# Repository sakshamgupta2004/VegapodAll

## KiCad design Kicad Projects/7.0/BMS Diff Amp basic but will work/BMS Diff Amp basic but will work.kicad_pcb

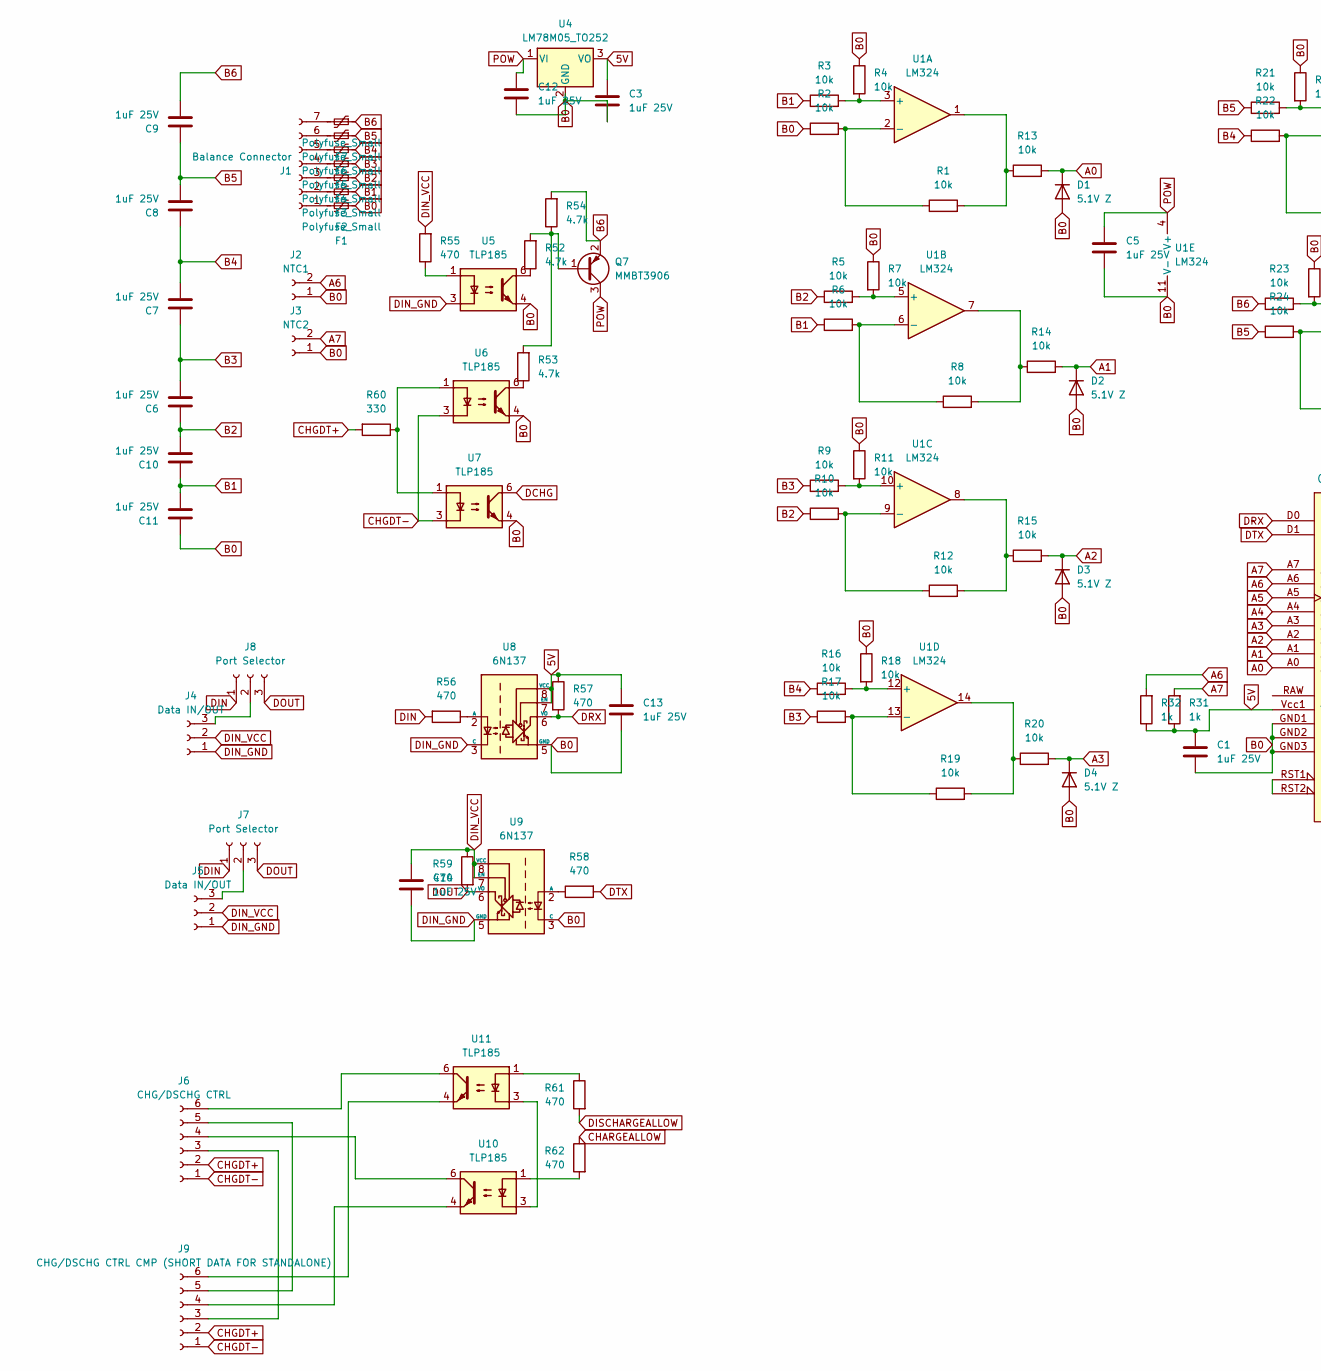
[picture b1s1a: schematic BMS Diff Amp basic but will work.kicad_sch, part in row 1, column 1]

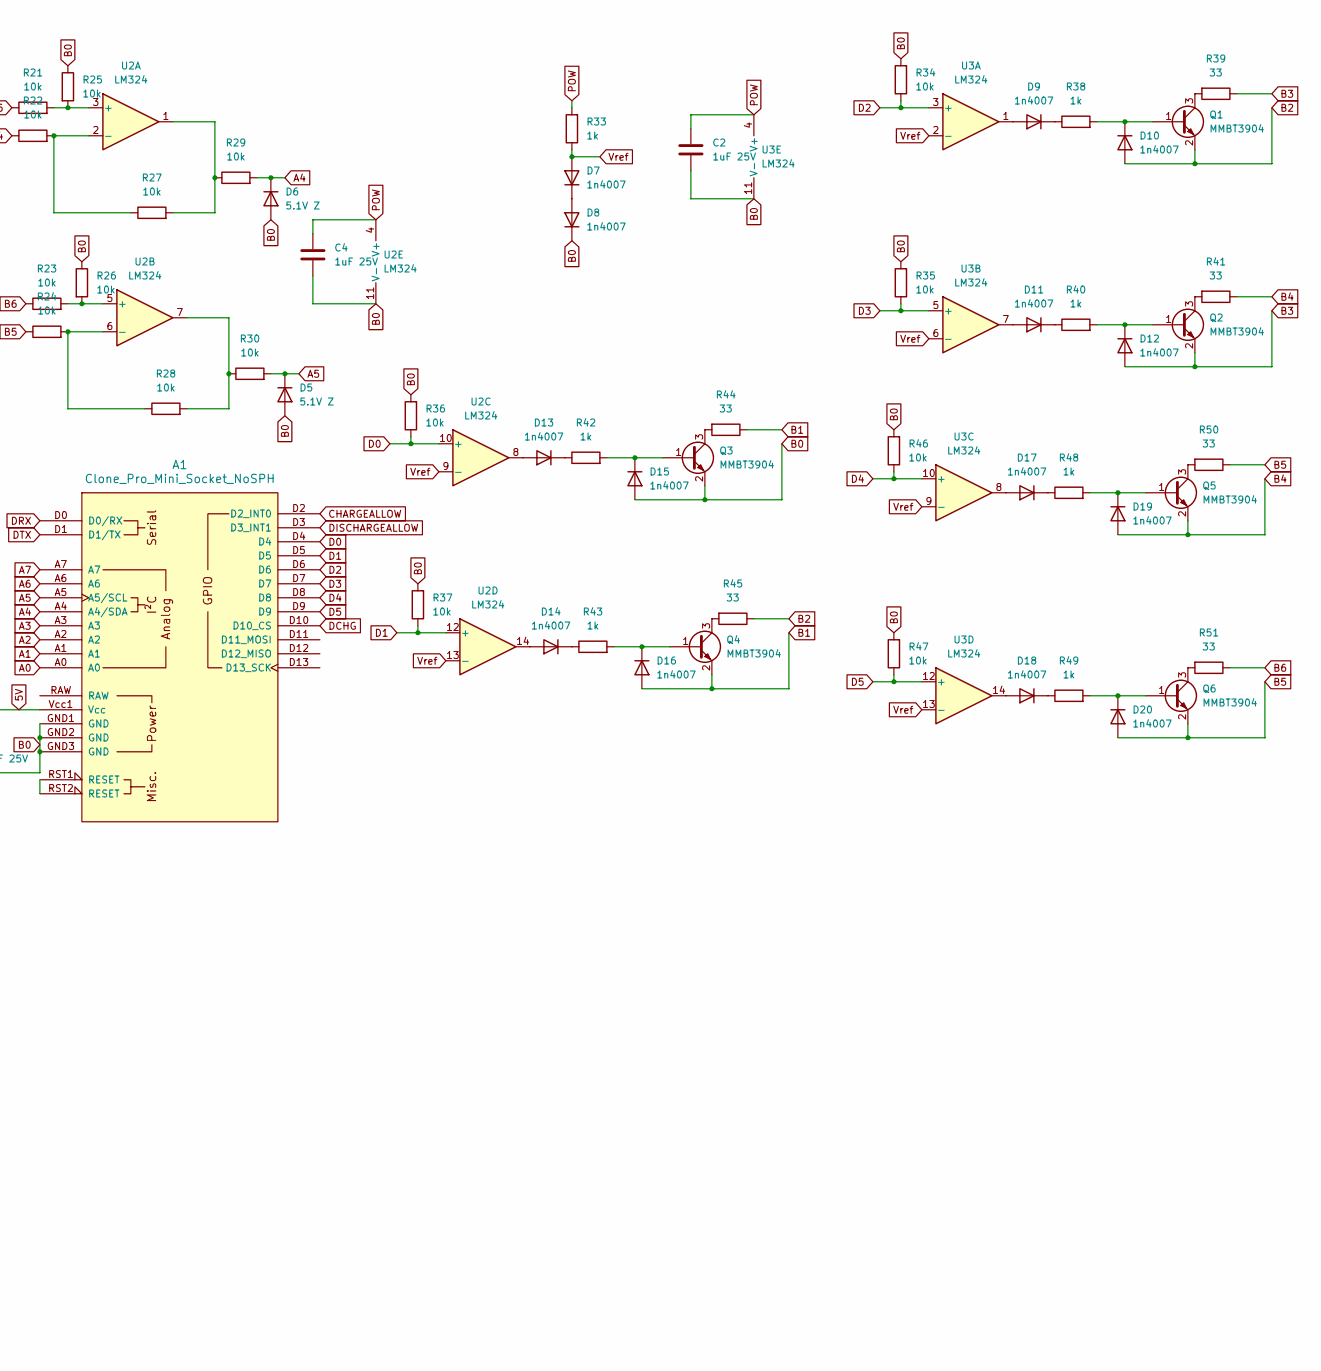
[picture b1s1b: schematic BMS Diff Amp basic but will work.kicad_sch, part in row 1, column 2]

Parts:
A1: Clone_Pro_Mini_Socket_NoSPH
C1, C2, C3, C4, C5, C6, C7, C8, C9, C10, C11, C12, C13, C14: 1uF 25V; C_1206_3216Metric_Pad1.33x1.80mm_HandSolder
D1, D2, D3, D4, D5, D6: 5.1V Z; D_SMA
D7, D8, D9, D10, D11, D12, D13, D14, D15, D16, D17, D18, D19, D20: 1n4007; D_SMA
F1, F2, F3, F4, F5, F6, F7: Polyfuse_Small; R_1206_3216Metric_Pad1.30x1.75mm_HandSolder
J1: Balance Connector; JST_XH_S7B-XH-A_1x07_P2.50mm_Horizontal
J2: NTC1; JST_XH_S2B-XH-A_1x02_P2.50mm_Horizontal
J3: NTC2; JST_XH_S2B-XH-A_1x02_P2.50mm_Horizontal
J4, J5: Data IN/OUT; JST_XH_S3B-XH-A-1_1x03_P2.50mm_Horizontal
J6: CHG/DSCHG CTRL; JST_XH_S6B-XH-A_1x06_P2.50mm_Horizontal
J7, J8: Port Selector; PinHeader_1x03_P1.00mm_Vertical
J9: CHG/DSCHG CTRL CMP (SHORT DATA FOR STANDALONE); JST_XH_B6B-XH-AM_1x06_P2.50mm_Vertical
Q1, Q2, Q3, Q4, Q5, Q6: MMBT3904; SOT-23
Q7: MMBT3906; SOT-23
R1, R2, R3, R4, R5, R6, R7, R8, R9, R10, R11, R12, R13, R14, R15, R16, R17, R18, R19, R20, R21, R22, R23, R24, R25, R26, R27, R28, R29, R30, R34, R35, R36, R37, R46, R47: 10k; R_0805_2012Metric_Pad1.20x1.40mm_HandSolder
R31, R32, R33, R38, R40, R42, R43, R48, R49: 1k; R_0805_2012Metric_Pad1.20x1.40mm_HandSolder
R39, R41, R44, R45, R50, R51: 33; R_1206_3216Metric_Pad1.30x1.75mm_HandSolder
R52, R53, R54: 4.7k; R_0805_2012Metric_Pad1.20x1.40mm_HandSolder
R55, R56, R57, R58, R59, R61, R62: 470; R_0805_2012Metric_Pad1.20x1.40mm_HandSolder
R60: 330; R_0805_2012Metric_Pad1.20x1.40mm_HandSolder
U1, U2, U3: LM324; SOIC-14_3.9x8.7mm_P1.27mm
U4: LM78M05_TO252; TO-252-2
U5, U6, U7, U10, U11: TLP185; SOIC-4_4.55x3.7mm_P2.54mm
U8, U9: 6N137; SOIC-8-1EP_3.9x4.9mm_P1.27mm_EP2.29x3mm

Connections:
5V: A1.Vcc1 (Vcc), C1.1, C3.1, C13.1, R31.1, R32.1, R57.1, U4.3 (VO), U8.7 (EN), U8.8 (VCC)
A0: A1.A0, D1.1 (K), R13.2
A1: A1.A1, D2.1 (K), R14.2
A2: A1.A2, D3.1 (K), R15.2
A3: A1.A3, D4.1 (K), R20.2
A4: A1.A4 (A4/SDA), D6.1 (K), R29.2
A5: A1.A5 (A5/SCL), D5.1 (K), R30.2
A6: A1.A6, J2.2, R32.2
A7: A1.A7, J3.2, R31.2
B0: A1.GND1 (GND), A1.GND2 (GND), A1.GND3 (GND), C1.2, C2.2, C3.2, C4.2, C5.2, C11.1, C12.2, C13.2, D1.2 (A), D2.2 (A), D3.2 (A), D4.2 (A), D5.2 (A), D6.2 (A), D8.1 (K), D15.2 (A), F1.1, J2.1, J3.1, Q3.2 (E), R2.1, R4.1, R7.1, R11.1, R18.1, R25.1, R26.1, R34.2, R35.2, R36.2, R37.2, R46.2, R47.2, U1.11 (V-), U2.11 (V-), U3.11 (V-), U4.2 (GND), U5.4, U6.4, U7.4, U8.5 (GND), U9.3 (C)
B1: C10.1, C11.2, D16.2 (A), F2.1, Q4.2 (E), R3.1, R6.1, R44.1
B2: C6.1, C10.2, D10.2 (A), F3.1, Q1.2 (E), R5.1, R10.1, R45.1
B3: C6.2, C7.1, D12.2 (A), F4.1, Q2.2 (E), R9.1, R17.1, R39.1
B4: C7.2, C8.1, D19.2 (A), F5.1, Q5.2 (E), R16.1, R22.1, R41.1
B5: C8.2, C9.1, D20.2 (A), F6.1, Q6.2 (E), R21.1, R24.1, R50.1
B6: C9.2, F7.1, Q7.2 (E), R23.1, R51.1, R54.2
CHARGEALLOW: A1.D2 (D2_INT0), R62.1
CHGDT+: J6.2, J9.2, R60.2
CHGDT-: J6.1, J9.1, U6.3, U7.3
D0: A1.D4, R36.1, U2.10 (+)
D1: A1.D5, R37.1, U2.12 (+)
D2: A1.D6, R34.1, U3.3 (+)
D3: A1.D7, R35.1, U3.5 (+)
D4: A1.D8, R46.1, U3.10 (+)
D5: A1.D9, R47.1, U3.12 (+)
DCHG: A1.D10 (D10_CS), U7.6
DIN: J7.1, J8.1, R56.2
DIN_GND: C14.2, J4.1, J5.1, U5.3, U8.3 (C), U9.5 (GND)
DIN_VCC: C14.1, J4.2, J5.2, R55.2, R59.1, U9.7 (EN), U9.8 (VCC)
DISCHARGEALLOW: A1.D3 (D3_INT1), R61.2
DOUT: J7.3, J8.3, R59.2, U9.6 (VO)
DRX: A1.D0 (D0/RX), R57.2, U8.6 (VO)
DTX: A1.D1 (D1/TX), R58.2
unnamed: A1.RST1 (RESET), A1.RST2 (RESET)
unnamed: D7.1 (K), D8.2 (A)
unnamed: D9.2 (A), U3.1
unnamed: D9.1 (K), R38.1
unnamed: D10.1 (K), Q1.1 (B), R38.2
unnamed: D11.2 (A), U3.7
unnamed: D11.1 (K), R40.1
unnamed: D12.1 (K), Q2.1 (B), R40.2
unnamed: D13.2 (A), U2.8
unnamed: D13.1 (K), R42.1
unnamed: D14.2 (A), U2.14
unnamed: D14.1 (K), R43.1
unnamed: D15.1 (K), Q3.1 (B), R42.2
unnamed: D16.1 (K), Q4.1 (B), R43.2
unnamed: D17.2 (A), U3.8
unnamed: D17.1 (K), R48.1
unnamed: D18.2 (A), U3.14
unnamed: D18.1 (K), R49.1
unnamed: D19.1 (K), Q5.1 (B), R48.2
unnamed: D20.1 (K), Q6.1 (B), R49.2
unnamed: F1.2, J1.1
unnamed: F2.2, J1.2
unnamed: F3.2, J1.3
unnamed: F4.2, J1.4
unnamed: F5.2, J1.5
unnamed: F6.2, J1.6
unnamed: F7.2, J1.7
unnamed: J4.3, J8.2
unnamed: J5.3, J7.2
unnamed: J6.3, J9.3
unnamed: J6.4, U10.6
unnamed: J6.5, J9.5
unnamed: J6.6, U11.6
unnamed: J9.4, U10.4
unnamed: J9.6, U11.4
unnamed: Q1.3 (C), R39.2
unnamed: Q2.3 (C), R41.2
unnamed: Q3.3 (C), R44.2
unnamed: Q4.3 (C), R45.2
unnamed: Q5.3 (C), R50.2
unnamed: Q6.3 (C), R51.2
unnamed: Q7.1 (B), R52.2, R53.2, R54.1
unnamed: R1.2, R13.1, U1.1
unnamed: R12.2, R15.1, U1.8
unnamed: R8.2, R14.1, U1.7
unnamed: R19.2, R20.1, U1.14
unnamed: R27.2, R29.1, U2.1
unnamed: R28.2, R30.1, U2.7
unnamed: R52.1, U5.6
unnamed: R53.1, U6.6
unnamed: R55.1, U5.1
unnamed: R60.1, U6.1, U7.1
unnamed: R61.1, U11.1
unnamed: R62.2, U10.1
unnamed: R3.2, R4.2, U1.3 (+)
unnamed: R1.1, R2.2, U1.2 (-)
unnamed: R5.2, R7.2, U1.5 (+)
unnamed: R6.2, R8.1, U1.6 (-)
unnamed: R9.2, R11.2, U1.10 (+)
unnamed: R10.2, R12.1, U1.9 (-)
unnamed: R16.2, R18.2, U1.12 (+)
unnamed: R17.2, R19.1, U1.13 (-)
unnamed: R21.2, R25.2, U2.3 (+)
unnamed: R22.2, R27.1, U2.2 (-)
unnamed: R23.2, R26.2, U2.5 (+)
unnamed: R24.2, R28.1, U2.6 (-)
unnamed: R56.1, U8.2 (A)
unnamed: R58.1, U9.2 (A)
unnamed: U10.3, U11.3
POW: C2.1, C4.1, C5.1, C12.1, Q7.3 (C), R33.2, U1.4 (V+), U2.4 (V+), U3.4 (V+), U4.1 (VI)
Vref: D7.2 (A), R33.1, U2.9 (-), U2.13 (-), U3.2 (-), U3.6 (-), U3.9 (-), U3.13 (-)

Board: 2 copper layers, 131 parts (0 on the bottom side), 104 nets, no tracks yet.

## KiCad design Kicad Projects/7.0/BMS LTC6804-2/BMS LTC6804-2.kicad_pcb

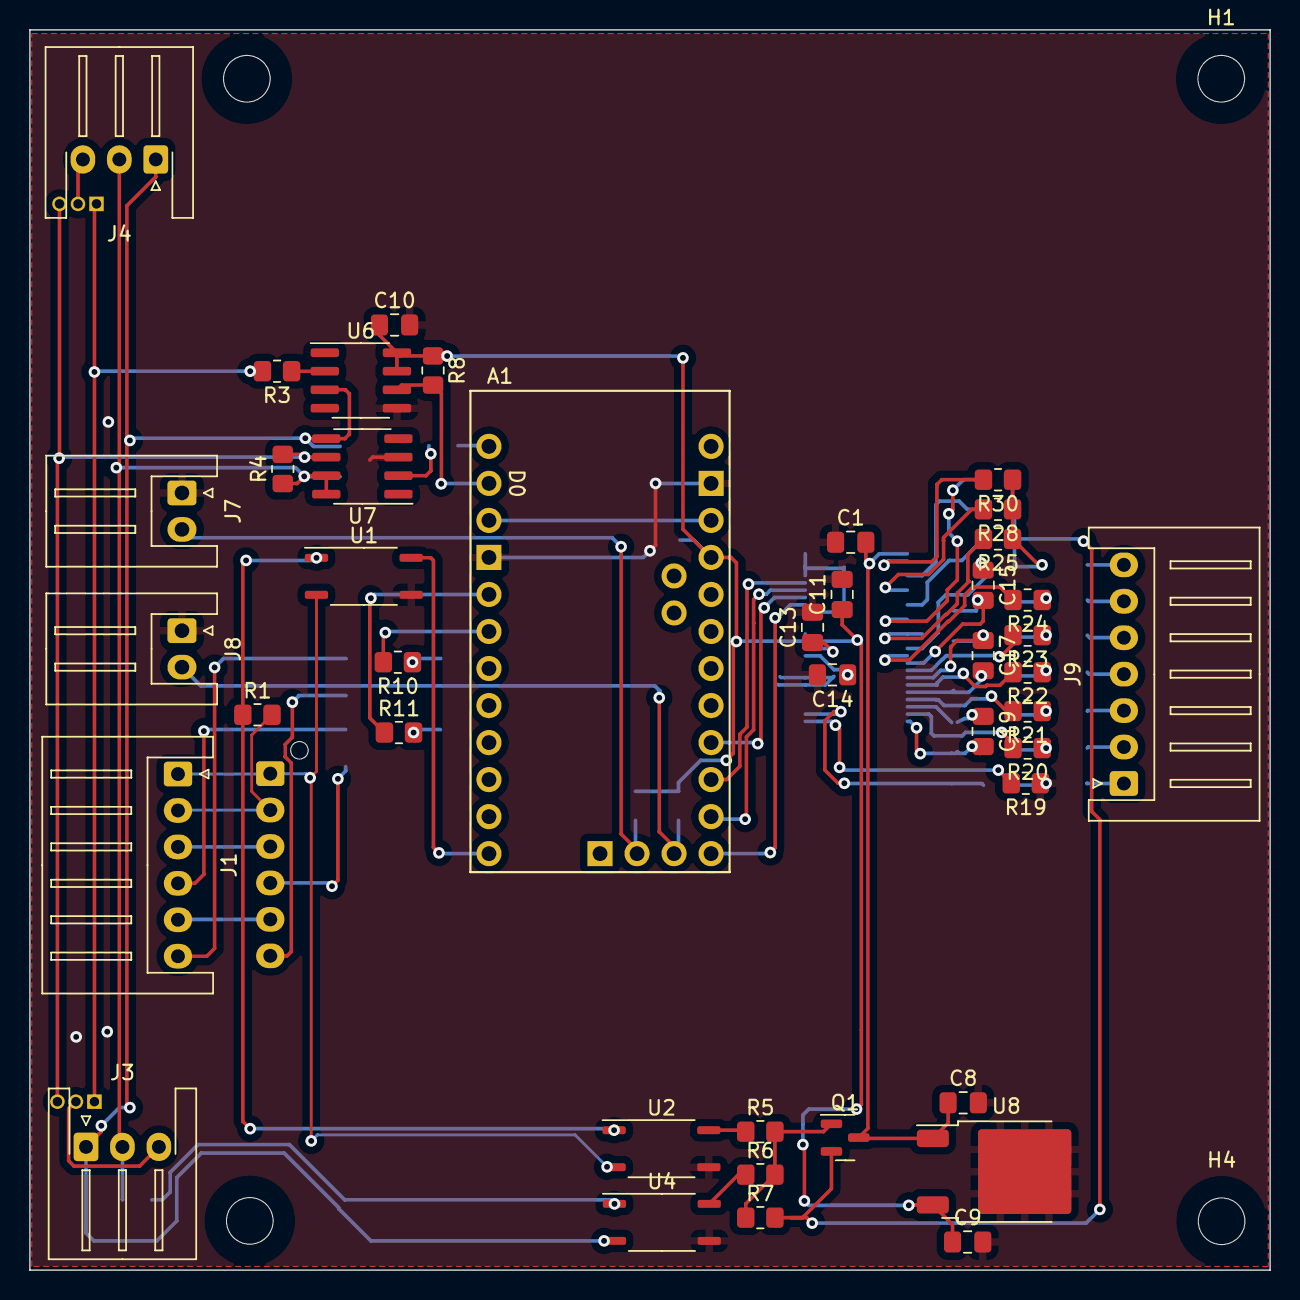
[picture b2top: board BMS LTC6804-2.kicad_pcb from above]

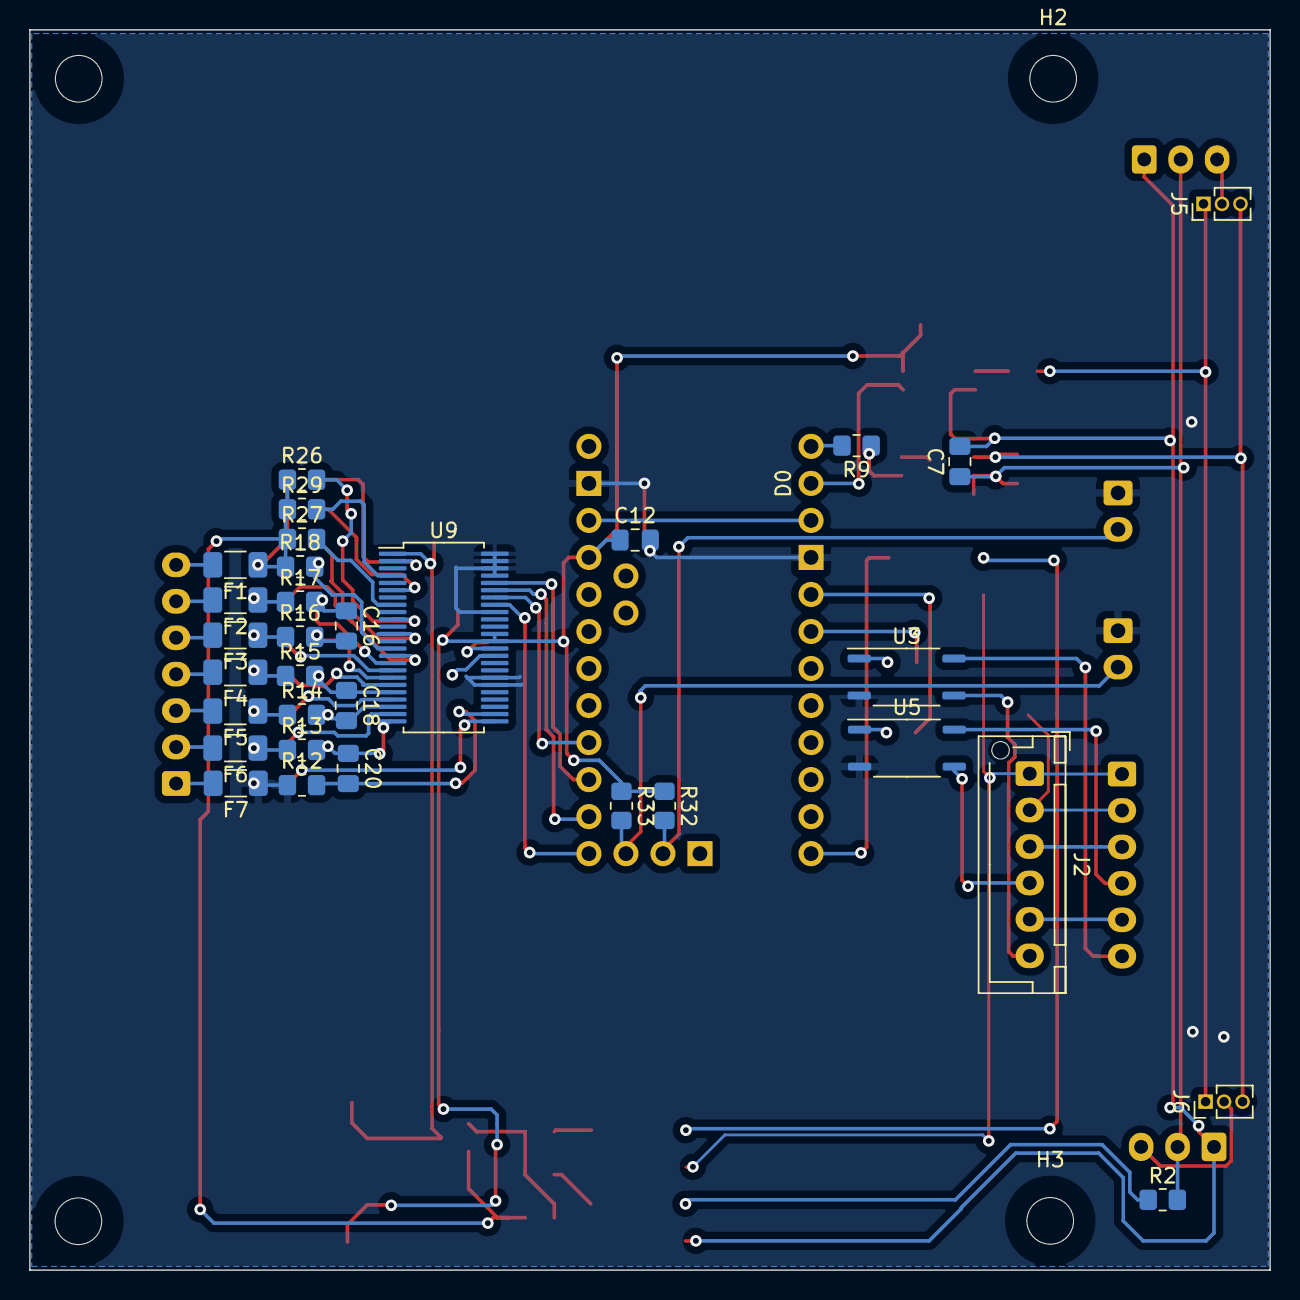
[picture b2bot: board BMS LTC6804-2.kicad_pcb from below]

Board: 2 copper layers, 85.1 x 85.1 mm, 78 parts (34 on the bottom side), 72 nets.

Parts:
A1: Clone_Pro_Mini_Socket_NoSPH
C1, C7, C8, C9, C10, C11, C12, C13, C14, C15, C16, C17, C18, C19, C20: 1uF 25V; C_0805_2012Metric_Pad1.18x1.45mm_HandSolder
F1, F2, F3, F4, F5, F6, F7: Polyfuse_Small; R_1206_3216Metric_Pad1.30x1.75mm_HandSolder
H1, H2, H3, H4: MountingHole; MountingHole_3.2mm_M3
J1: CHG/DSCHG CTRL; JST_XH_S6B-XH-A_1x06_P2.50mm_Horizontal
J2: CHG/DSCHG CTRL CMP (SHORT DATA FOR STANDALONE); JST_XH_B6B-XH-AM_1x06_P2.50mm_Vertical
J3, J4: Data IN/OUT; JST_XH_S3B-XH-A-1_1x03_P2.50mm_Horizontal
J5, J6: Port Selector; PinHeader_1x03_P1.27mm_Vertical
J7: NTC1; JST_XH_S2B-XH-A_1x02_P2.50mm_Horizontal
J8: NTC2; JST_XH_S2B-XH-A_1x02_P2.50mm_Horizontal
J9: Balance Connector; JST_XH_S7B-XH-A_1x07_P2.50mm_Horizontal
Q1: MMBT3906; SOT-23
R1: 330; R_0805_2012Metric_Pad1.20x1.40mm_HandSolder
R2, R3, R4, R8, R9, R10, R11: 470; R_0805_2012Metric_Pad1.20x1.40mm_HandSolder
R5, R6, R7: 4.7k; R_0805_2012Metric_Pad1.20x1.40mm_HandSolder
R12, R13, R14, R15, R16, R17, R18, R25, R26, R27, R28, R29, R30: 100; R_0805_2012Metric_Pad1.20x1.40mm_HandSolder
R19, R20, R21, R22, R23, R24: 22; R_0805_2012Metric_Pad1.20x1.40mm_HandSolder
R32, R33: 1k; R_0805_2012Metric_Pad1.20x1.40mm_HandSolder
U1, U2, U3, U4, U5: TLP185; SOIC-4_4.55x3.7mm_P2.54mm
U6, U7: 6N137; SOIC-8_3.9x4.9mm_P1.27mm
U8: LM78M05_TO252; TO-252-2
U9: LTC6804-1; SSOP-48_5.3x12.8mm_P0.5mm

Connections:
5V: A1.Vcc1 (Vcc), C9.1, C10.1, C11.1, C12.1, R8.1, R32.1, R33.1, U6.7 (EN), U6.8 (VCC), U8.3 (VO), U9.36 (SWTEN), U9.37 (VREG)
A6: A1.A6, J7.2, R32.2
A7: A1.A7, J8.2, R33.2
B0: A1.GND1 (GND), A1.GND2 (GND), C1.1, C8.2, C9.2, C10.2, C11.2, C12.2, C13.2, C14.2, F7.1, J7.1, J8.1, R12.1, R19.1, U1.4, U2.4, U3.3, U4.4, U5.3, U6.5 (GND), U7.3 (C), U8.2 (GND), U9.30 (V-), U9.31 (V-), U9.40 (ISOMD), U9.45 (IBIAS), U9.46 (ICMP), U9.47 (IMB), U9.48 (IPB)
B1: F6.1, R13.1, R20.1
B2: F5.1, R14.1, R21.1
B3: F4.1, R15.1, R22.1
B4: F3.1, R16.1, R23.1
B5: F2.1, R17.1, R24.1
B6: F1.1, Q1.2 (E), R7.2, R18.1, R25.1, R26.1, R27.1, R28.1, R29.1, R30.1
CHARGEALLOW: A1.D2 (D2_INT0), R11.1
CHGDT+: J1.2, J2.2, R1.2
CHGDT-: J1.1, J2.1, U1.3, U2.3
DCHG: A1.D9, U1.6
DIN: J5.1, J6.1, R3.2
DIN_GND: C7.2, J3.1, J4.1, U4.3, U6.3 (C), U7.5 (GND)
DIN_VCC: C7.1, J3.2, J4.2, R2.2, R4.1, U7.7 (EN), U7.8 (VCC)
DISCHARGEALLOW: A1.D3 (D3_INT1), R10.2
DOUT: J5.3, J6.3, R4.2, U7.6 (VO)
DRX: A1.D0 (D0/RX), R8.2, U6.6 (VO)
DTX: A1.D1 (D1/TX), R9.2
MISO: A1.D12 (D12_MISO), U9.44 (SDO(NC))
MOSI: A1.D11 (D11_MOSI), U9.43 (SDI(NC))
unnamed: A1.RST1 (RESET), A1.RST2 (RESET)
unnamed: J1.3, J2.3
unnamed: J1.4, U5.6
unnamed: J1.5, J2.5
unnamed: J1.6, U3.6
unnamed: J2.4, U5.4
unnamed: J2.6, U3.4
unnamed: J3.3, J6.2
unnamed: J4.3, J5.2
unnamed: F7.2, J9.1
unnamed: F6.2, J9.2
unnamed: F5.2, J9.3
unnamed: F4.2, J9.4
unnamed: F3.2, J9.5
unnamed: F2.2, J9.6
unnamed: F1.2, J9.7
unnamed: Q1.1 (B), R5.2, R6.2, R7.1
unnamed: R1.1, U1.1, U2.1
unnamed: R2.1, U4.1
unnamed: R5.1, U2.6
unnamed: R6.1, U4.6
unnamed: R10.1, U3.1
unnamed: R11.2, U5.1
unnamed: R3.1, U6.2 (A)
unnamed: R9.1, U7.2 (A)
unnamed: C20.2, R12.2, U9.26 (C0)
unnamed: C19.2, C20.1, R13.2, U9.24 (C1)
unnamed: C18.2, C19.1, R14.2, U9.22 (C2)
unnamed: C17.2, C18.1, R15.2, U9.20 (C3)
unnamed: C16.2, C17.1, R16.2, U9.18 (C4)
unnamed: C15.2, C16.1, R17.2, U9.16 (C5)
unnamed: C15.1, R18.2, U9.14 (C6)
unnamed: R25.2, U9.12 (C7)
unnamed: R26.2, U9.10 (C8)
unnamed: R27.2, U9.8 (C9)
unnamed: R28.2, U9.6 (C10)
unnamed: R29.2, U9.4 (C11)
unnamed: R30.2, U9.2 (C12)
unnamed: R19.2, U9.25 (S1)
unnamed: R20.2, U9.23 (S2)
unnamed: R21.2, U9.21 (S3)
unnamed: R22.2, U9.19 (S4)
unnamed: R23.2, U9.17 (S5)
unnamed: R24.2, U9.15 (S6)
unnamed: C13.1, U9.35 (VREF1)
unnamed: C14.1, U9.34 (VREF2)
POW: C1.2, C8.1, Q1.3 (C), U8.1 (VI), U9.1 (V+)
SCK: A1.D13 (D13_SCK), U9.42 (SCK(IPA))
SS: A1.D10 (D10_CS), U9.41 (CSB(IMA))

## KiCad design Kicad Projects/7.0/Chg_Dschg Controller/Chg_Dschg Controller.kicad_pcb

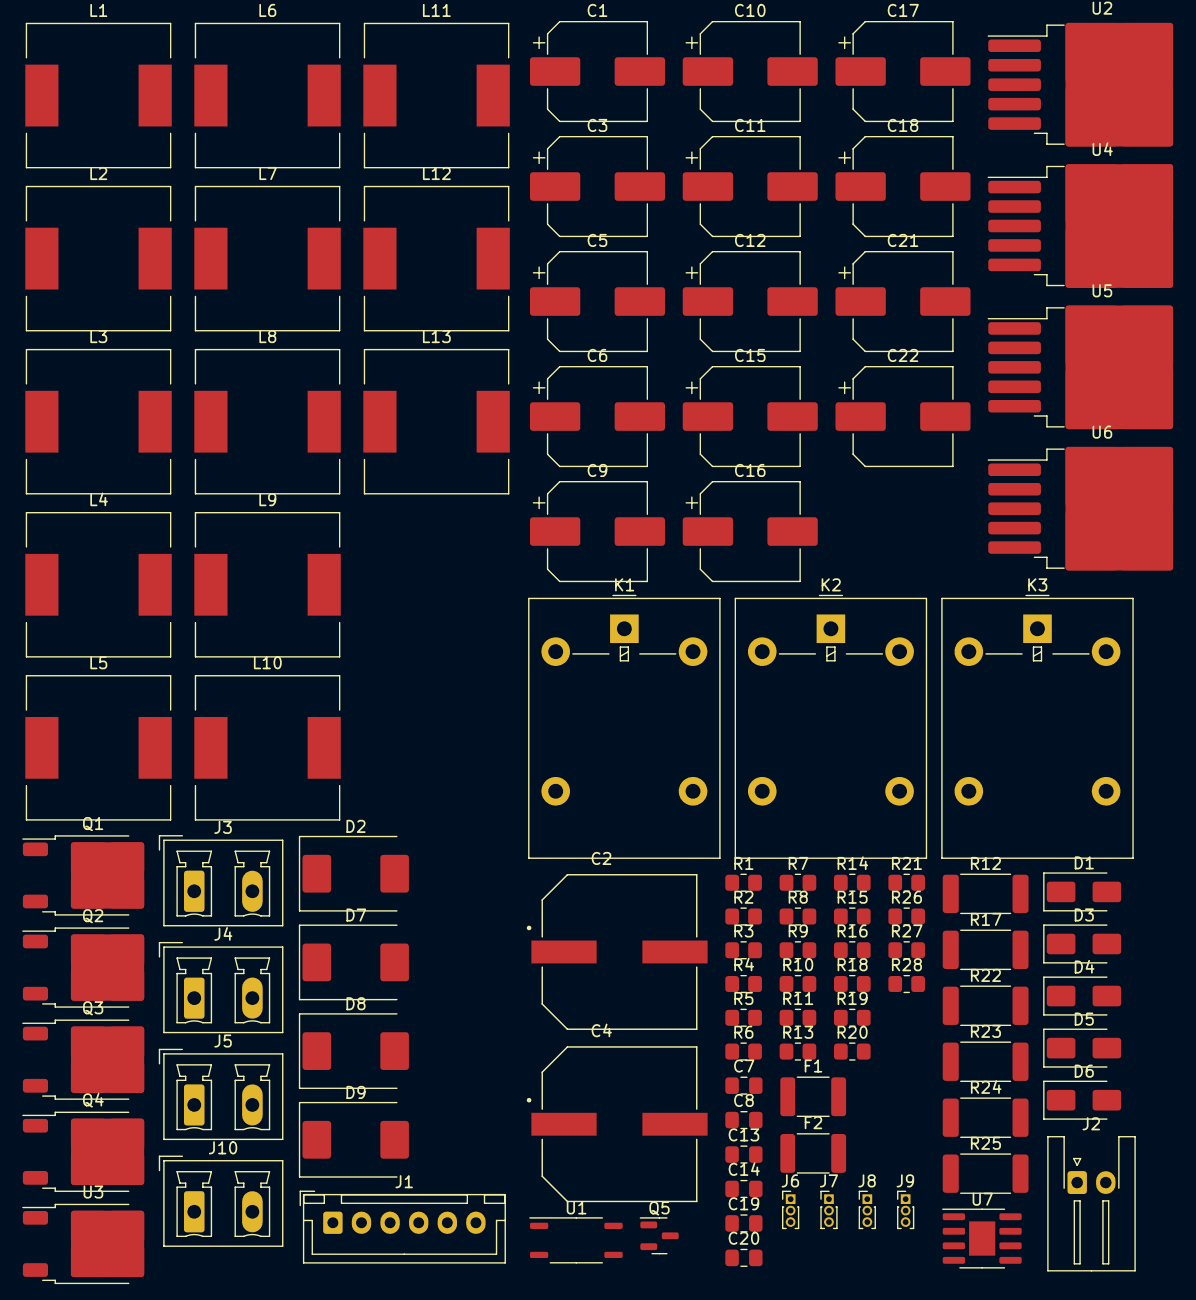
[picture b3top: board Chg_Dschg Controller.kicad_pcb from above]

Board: 2 copper layers, 99 parts (0 on the bottom side), 48 nets, no tracks yet.

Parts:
C1, C3, C5, C6, C9, C10, C11, C12, C15, C16, C17, C18, C21, C22: 100uF 50V; CP_Elec_8x10.5
C2, C4: 25V 1000uF; CAP_EEEFK1E102AQ
C7, C8, C13, C14, C19, C20: 1uF 50V; C_0805_2012Metric_Pad1.18x1.45mm_HandSolder
D1, D3, D4, D5, D6: 1n4007; D_SMA
D2, D7, D8, D9: SS56; D_SMC
F1, F2: 5A 1808; R_1812_4532Metric_Pad1.30x3.40mm_HandSolder
J1: Slave socket; JST_XH_B6B-XH-A_1x06_P2.50mm_Vertical
J2: Electronics; JST_XH_S2B-XH-A-1_1x02_P2.50mm_Horizontal
J3: Charger; PhoenixContact_MCV_1,5_2-G-5.08_1x02_P5.08mm_Vertical
J4: Battery; PhoenixContact_MCV_1,5_2-G-5.08_1x02_P5.08mm_Vertical
J5: Contactor; PhoenixContact_MCV_1,5_2-G-5.08_1x02_P5.08mm_Vertical
J6: NO/NC Contactor; PinHeader_1x03_P1.00mm_Vertical
J7: NC/NO Charge; PinHeader_1x03_P1.00mm_Vertical
J8: NO/NC Charge-; PinHeader_1x03_P1.00mm_Vertical
J9: NO/NC Charge+; PinHeader_1x03_P1.00mm_Vertical
J10: Boost OUT; PhoenixContact_MCV_1,5_2-G-5.08_1x02_P5.08mm_Vertical
K1, K2, K3: Relay_SPDT; Relay_SPDT_Omron-G5LE-1
L1: CDRH127 100u; L_12x12mm_H8mm
L2, L3, L4, L5, L6, L7, L8, L9, L10, L11, L12, L13: CDRH127 47u; L_12x12mm_H8mm
Q1, Q2, Q3, Q4: IRFR120NTRPBF; TO-252-2
Q5: MMBT5551L; SOT-23
R1: 470; R_0805_2012Metric_Pad1.20x1.40mm_HandSolder
R2, R7: 10k; R_0805_2012Metric_Pad1.20x1.40mm_HandSolder
R3, R8, R9, R11, R15, R16, R20, R21, R26, R28: 1k; R_0805_2012Metric_Pad1.20x1.40mm_HandSolder
R4, R5: 100k; R_0805_2012Metric_Pad1.20x1.40mm_HandSolder
R6, R10, R13, R14, R18, R19: 39k; R_0805_2012Metric_Pad1.20x1.40mm_HandSolder
R12, R17, R22, R23, R24, R25: 0.1Ohm 1W; R_2512_6332Metric_Pad1.40x3.35mm_HandSolder
R27: 29k; R_0805_2012Metric_Pad1.20x1.40mm_HandSolder
U1: TLP185; SOIC-4_4.55x3.7mm_P2.54mm
U2: LM2576HVS-12; TO-263-5_TabPin3
U3: LM78M05_TO252; TO-252-2
U4, U5, U6: XL6019; TO-263-5_TabPin3
U7: LM393; SOIC-8-1EP_3.9x4.9mm_P1.27mm_EP2.29x3mm

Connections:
+BATT: C1.1, F2.2, J9.2, R3.1, R8.1, U2.1 (VIN)
-BATT: F1.2, K1.1, Q1.3 (S), Q2.3 (S), R2.1, R7.1
/5V: C4.1, J1.2, R27.1, U3.3 (VO)
/12V: C2.1, D1.1 (K), D3.1 (K), D4.1 (K), J5.2, K1.5, K2.5, K3.5, L1.2, U2.4 (FB)
/Drain1: C1.2, C2.2, D2.2 (A), Q1.2 (D), Q2.2 (D), Q3.3 (S), Q4.3 (S), R4.1, R5.1, U2.3 (GND), U2.5 (~ON/OFF)
/Gate1: D6.2 (A), J1.3, Q2.1 (G), R2.2
/NCR1: J6.3, J7.3, K1.3
/NOR1: J6.1, J7.1, K1.4
BOOSTIN+: C3.1, C5.1, C6.1, C7.1, C11.1, C12.1, C13.1, C17.1, C18.1, C19.1, J3.2, L2.1, L3.1, L6.1, L7.1, L10.1, L11.1, U3.1 (VI), U4.4 (VIN), U5.4 (VIN), U6.4 (VIN), U7.8 (V+)
BOOSTIN-: C3.2, C4.2, C5.2, C6.2, C7.2, C8.2, C9.2, C10.2, C11.2, C12.2, C13.2, C14.2, C15.2, C16.2, C17.2, C18.2, C19.2, C20.2, C21.2, C22.2, J1.1, J3.1, Q5.2 (E), R9.2, R11.2, R15.2, R16.2, R20.2, R21.2, R23.1, R24.1, R25.1, R26.2, U3.2 (GND), U4.1 (GND), U5.1 (GND), U6.1 (GND), U7.4 (V-)
BOOSTOUT+: J10.2, K3.1, R12.2, R17.2, R22.2
BOOSTOUT-: J10.1, K2.1, R23.2, R24.2, R25.2, U7.3 (+)
CCEN: Q5.3 (C), U4.2 (EN), U5.2 (EN), U6.2 (EN)
unnamed: D1.2 (A), J5.1, J6.2
unnamed: D2.1 (K), L1.1, U2.2 (OUT)
unnamed: D3.2 (A), K1.2, Q3.2 (D)
unnamed: D4.2 (A), K2.2, K3.2, Q4.2 (D)
unnamed: D5.2 (A), J1.5, Q1.1 (G), R7.2
unnamed: D5.1 (K), Q3.1 (G), R5.2
unnamed: D6.1 (K), Q4.1 (G), R4.2
unnamed: D7.2 (A), L4.2, L5.2, U4.3 (SW)
unnamed: C8.1, C9.1, C10.1, D7.1 (K), R6.1, R10.1, R12.1
unnamed: D8.2 (A), L8.2, L9.2, U5.3 (SW)
unnamed: C14.1, C15.1, C16.1, D8.1 (K), R13.1, R14.1, R17.1
unnamed: D9.2 (A), L12.2, L13.2, U6.3 (SW)
unnamed: C20.1, C21.1, C22.1, D9.1 (K), R18.1, R19.1, R22.1
unnamed: J1.4, R3.2
unnamed: J1.6, U1.4
unnamed: J2.1, U1.3
unnamed: J2.2, R1.2
unnamed: F1.1, J4.1
unnamed: F2.1, J4.2
unnamed: J7.2, J8.2
unnamed: J8.1, K2.4
unnamed: J8.3, K2.3
unnamed: J9.1, K3.4
unnamed: J9.3, K3.3
unnamed: L2.2, L3.2, L4.1, L5.1
unnamed: L6.2, L7.2, L8.1, L9.1
unnamed: L10.2, L11.2, L12.1, L13.1
unnamed: Q5.1 (B), R28.2
unnamed: R1.1, U1.1
unnamed: R8.2, U1.6
unnamed: R28.1, U7.1
unnamed: R6.2, R9.1, R10.2, R11.1, U4.5 (FB)
unnamed: R13.2, R14.2, R15.1, R16.1, U5.5 (FB)
unnamed: R18.2, R19.2, R20.1, R21.1, U6.5 (FB)
unnamed: R26.1, R27.2, U7.2 (-)
